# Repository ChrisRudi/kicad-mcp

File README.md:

# Claude für KiCad — Chat-Copilot im PCB-Editor + 186-Tool-MCP-Server

**Claude als dockbares Chat-Panel direkt in KiCad 10** — mit klickbaren
Board-Links, 34 Ein-Klick-Super-Features und einem warmen lokalen MCP-Server —
plus derselbe Server als klassischer [Model Context Protocol](https://modelcontextprotocol.io/)-Endpunkt
für Claude Code, Claude Desktop, Cursor und jeden anderen MCP-Client.

> Deutsche Übersetzung dieser README: [README.de.md](README.de.md).
> (This README is bilingual-pragmatic: product sections in German — the
> plugin UI language — tool/API sections in English.)

---

## What Makes This Different

Most KiCad MCP servers are tool collections. This one is a **product**:

- **💬 Chat dockt in den PCB-Editor** — ein Toolbar-Button öffnet „Claude für
  KiCad" als natives AUI-Panel. Jede Nachricht läuft als headless
  Claude-Code-Turn gegen das **offene Board** (keine API-Keys — dein
  Claude-Code-Login).
- **🔗 Klickbare Antworten (Cross-Probe)** — Referenzen, Netze, Pins, Layer und
  Koordinaten in der Antwort sind Links: Klick markiert + zoomt im Editor.
  Änderungen kommen mit Quittung („✎ geändert: … · 📍 zeigen") und sichtbarem
  **Undo**.
- **✨ 34 Super-Features als Ein-Klick-Buttons** — Dinge, die KiCad
  *prinzipiell* nicht kann, weil sie Bedeutung/Norm-/Datenblatt-Wissen
  brauchen: Entwirren mit Geister-Vorschau, Datenblatt-Abgleich, semantischer
  Design-Wächter, Stromtragfähigkeit (IPC-2221), Schutzklassen (IEC
  61140/60664), echte SPICE-Simulation, BOM-Konsolidierung, DFM-Check … —
  Roadmap + ehrliche Grenzen in [docs/superfeatures.md](docs/superfeatures.md).
- **🔥 Warm-Server** — optional läuft der 186-Tool-Server **einmal pro
  KiCad-Sitzung** als lokaler HTTP-Dienst statt pro Nachricht neu zu starten
  (`KICAD_MCP_TRANSPORT=http`): kein Kaltstart, kein
  „MCP nicht verbunden"-Wackler; Health-Check pro Zug, Auto-Restart,
  Bearer-Token, sauberer Teardown.
- **📐 Generierung, nicht nur Analyse** — Schaltplan + PCB aus
  JSON-Spezifikationen, komplette Projekte aus **ESPHome-YAML**, LTspice-Import,
  Datenblatt-PDF → Applikations-Schaltungsblock.
- **🧭 Ehrlichkeits-Disziplin** — Normwerte (IEC 60664, Fab-Kataloge) leben als
  **datierte, kuratierte Snapshots** im Werkzeug statt im Modellgedächtnis;
  Mutationen laufen nur nach ausdrücklichem **Go**; jede v1-Grenze wird im
  Bericht benannt („Vorprüfung, keine Zertifizierung").
- **🛡️ Gehärtet gegen die fiesen Fälle** — Geister-Editor-Abwehr mit
  Registry + Selbstheilung der Links, Busy-Backoff statt Fehlstart,
  Prozess-Aufräumen bei KiCad-Exit, WSL↔Windows-Pfad-Transparenz.

---

## Die Super-Features (Auszug)

Jeder Button dispatcht einen kanonischen, geführten Auftrag — mit der aktuellen
Editor-**Auswahl** als Wirkbereich (nichts markiert = ganzes Board). Vollständige
Liste + v1-Grenzen: [docs/superfeatures.md](docs/superfeatures.md).

| Button | Was er tut | Fundament |
|---|---|---|
| 🧶 Entwirren | Ratsnest-Entkreuzung: im Kopf lösen, Score vorher/nachher, **Geister-Vorschau auf MCP.Skizze**, ein Batch-Move nach Go | `evaluate_layout`-Scorer |
| 📄 Datenblatt-Abgleich | Beschaltung eines ICs gegen sein PDF (Entkopplung, Pins, fehlende Bauteile) | `review_ic_against_datasheet` |
| 🛡️ Design-Wächter | Semantischer ERC: I²C ohne Pull-ups, Quarz ohne Load-Caps, Entkopplungs-Nähe | `audit_design`-Regel-Registry |
| 🔥 Stromtragfähigkeit | Track-Breiten gegen Design-Strom (IPC-2221, Innenlagen strenger) | `check_ampacity` (#184) |
| 🔌 Schutzklassen | Isolationskonzept nach IEC 61140: geforderte Kriech-/Luftstrecken je Spannungsgrenze aus datiertem Norm-Snapshot vs. Ist-Abstände | `get_safety_spacing` (#186) |
| 📈 Simulation | Echte ngspice-Ausführung des vom Agenten gebauten SPICE-Decks; analytischer Fallback | `run_spice_sim` (#185) |
| 💰 BOM-Konsolidierung / 🏭 Fab-Standardteile | E-Reihen-Standardisierung, No-Load-Fee-Vorzugsteile inkl. Ersparnis | `consolidate_bom`, `suggest_preferred_parts` |
| 🔎 Test-Punkt-Wächter | Kritische Netze ohne Prüfpunkt-Zugang, Abdeckung in % | `audit_test_points` |
| 👁️ Mitdenken-Review | Bewertet deine letzten Hand-Änderungen am offenen Board | `live_summarize_user_changes` |

Dazu: Bus-Radar, Board erklären, Netz-Navigator, Pin-Tausch (Vorschläge),
Ausrichten & Anordnen, Polar-Board, Skizzen-Layer/-Dirigent, Thermik,
Betriebstemperatur, Slew-Rate, Impedanz, DFM-Check, Kosten-Schätzer,
SPICE-Modelle, Bauteil-Sourcing, Foto→Schaltung, Sicherheitsabstände,
Firmware-Pinmap, MLCC-Derating, Silk-Aufräumen, Datenblatt→Schaltung.

---

## ▶ Demo — 10 Referenz-Bausätze

Der **`▶ Demo ▾`**-Knopf im Chat-Panel öffnet ein Menü mit 10 kuratierten
Bausätzen. Jeder fährt den vollen Ablauf **Idee → Schaltplan → Berechnung →
Platine** ab und lässt anschließend die zum Bausatz passende
Super-Feature-Pipeline laufen (z. B. Bus-Radar → semantischer ERC → Impedanz).
So sieht man in einem Klick, was der Copilot produziert — ohne eigenes Board.
Daneben liegt eine **🔧 Schnell-Demo (Testboard)** für den 10-Sekunden-Blick.

**Reife-Label je Bausatz** — zwei unabhängige Achsen, ein Symbol
(`demo_kits.stage`, ein grüner Test, keine Meinung):

- **⭐ Prime-Time** — *beide* Achsen grün: Schaltplan Pin-für-Pin
  datenblatt-geprüft **und** Platine 0 DRC / 0 offene Netze.
- **✅ Verified** — *eine* Achse grün (die andere bewusst oder noch offen).
- **🔬 In Arbeit** — noch keine Achse grün.

**Stand: 8 ⭐ / 2 ✅ / 0 🔬** — alle 10 Platinen bauen DRC-sauber (0 Fehler,
0 offene Netze); Datenblatt-Belege je Bausatz in
[docs/kit_datasheet_reviews.md](docs/kit_datasheet_reviews.md).

| Bausatz | Reife | Was ihn ausmacht |
|---|---|---|
| 🔊 Audioverstärker | ⭐ | Chip-Endstufe mit OpAmp-Eingangsstufe — der Analog-Klassiker (LM386). |
| 🔌 USB-C Sensor-Hub | ⭐ | MCU mit I²C/SPI-Sensoren + USB-C (STM32, LQFP-48) — das Digital-Arbeitstier. |
| ⚡ AC-DC-Netzteil | ⭐ | Offline-Flyback 230 V → 5 V (TNY268) — das Netzspannungs-Projekt. |
| ⚙️ Motor-Treiber | ⭐ | Gate-Driver mit MOSFET-Brücke und MCU (DRV8871) — Leistungselektronik. |
| 📉 Buck-Wandler-Modul | ⭐ | DC-DC-Abwärtswandler mit IC, Spule, Filter-Cs (MP1584). |
| ⊙ LED-Ring | ⭐ | Adressierbare WS2812-LEDs auf rundem Board (Polar-Layout). |
| 🏭 Serienreife & Kosten | ⭐ | Dichtes Breakout mit vielen R/C (74HC595) — Fokus Fertigung & Kosten. |
| 🪄 Datenblatt & Foto → Schaltung | ⭐ | Meta-Demo: wie ein Bausatz überhaupt entsteht. |
| 🌐 Ethernet-Gerät | ✅ | MCU + Ethernet-PHY + RJ45 — Platine ist saubere Referenz (0/0); Schaltplan-Datenblatt-Prüfung noch offen. |
| ✏️ Skizze → Kupfer | ✅ | Kleiner Leistungspfad, den man interaktiv mit Hilfe routet — *bewusst* Skizze. |

Die 10 Spec-JSONs liegen unter `kicad_mcp/resources/data/demo_kits/`; drei
(Buck, Motor, Audio) sind seit 0.27.0 **Build-Artefakte** aus Circuit-Block +
Rezept (eine Quelle, `tests/test_kit_compose.py` wacht). Der ganze Fahrplan,
wie aus den Startplatzierungen 0/0-Platinen wurden:
[docs/roadmap.md](docs/roadmap.md).

---

## Install

### A) Das KiCad-Plugin (empfohlen — Chat + alles oben)

1. Hole `claude_kicad-<version>-pcm.zip`:
   - **Download** aus dem neuesten [GitHub Release](https://github.com/ChrisRudi/kicad-mcp/releases), **oder**
   - **selbst bauen:** `python make_pcm_zip.py` → `dist/claude_kicad-<version>-pcm.zip`
     (pure stdlib, kein KiCad nötig). Alternativ: `install_plugin.bat` /
     `install_plugin.sh` installieren direkt aus dem Repo-Checkout.
2. KiCad: **Plugin- und Content-Manager → Aus Datei installieren…** → Zip wählen.
   (Nicht das GitHub-Auto-Zip nehmen — PCM lehnt den `<repo>-<branch>/`-Wrapper ab.)
3. KiCad neu starten → neuer Toolbar-Button im PCB-Editor. Der erste Klick
   öffnet die Einrichtungs-Checkliste: installiert die Python-Abhängigkeiten in
   einen plugin-eigenen `_deps`-Ordner, aktiviert KiCads IPC-API und hilft beim
   Claude-Code-Login. Danach: Board öffnen, Button klicken, chatten.

Voraussetzungen: **KiCad 10.0**, [Claude Code CLI](https://claude.ai/code)
(Login per Subscription, kein API-Key). Updates liefert der eingebaute
Self-Updater (Versionsanzeige im Panel-Titel; Historie: [plugin/VERSIONS.md](plugin/VERSIONS.md)).

### B) Der MCP-Server für externe Clients

```bash
git clone <this-repo>
cd kicad-mcp

# Linux / WSL / macOS:
./install.sh
# Windows (PowerShell):
.\install.ps1
```

Der Installer prüft KiCad 10, registriert den Server bei Claude Code (falls
`claude` installiert) und druckt Copy-Paste-JSON für Claude Desktop, Cursor,
Windsurf, VS Code, Continue.dev und Zed. Start-Kommandos:
`start_mcp_wsl.sh` (Linux/WSL/macOS) bzw. `start_mcp.bat` (Windows).
Der Server läuft unter **KiCads gebündeltem Python** — keine separate
Python-Installation nötig. Falls KiCad nicht gefunden wird:
`KICAD_PYTHON_PATH` auf die `python.exe` im KiCad-`bin/` setzen.

---

## Warm-Server & Umgebungs-Schalter

Standard-Transport ist `stdio` (Claude startet den Server pro Nachricht).
Mit `KICAD_MCP_TRANSPORT=http` hält das Plugin **einen** persistenten lokalen
Server pro KiCad-Sitzung warm (strikt `127.0.0.1`, zufälliges Bearer-Token,
Pidfile-Verwaltung, Health-Check je Zug, `atexit`-Teardown). Rollback ist
jederzeit ein Env-Wort.

| Variable | Wirkung |
|---|---|
| `KICAD_MCP_TRANSPORT` | `stdio` (Default) oder `http` (Warm-Server) |
| `KICAD_MCP_HTTP_HOST` / `_PORT` / `_TOKEN` | HTTP-Bind + Token (setzt normal das Plugin) |
| `KICAD_MCP_NGSPICE` | Pfad zum ngspice-Binary für `run_spice_sim` (sonst PATH/KiCad-bin) |
| `KICAD_MCP_NO_AUTO_OPEN` | `1` = Server darf nie selbst einen Editor starten (setzt das Plugin automatisch — verhindert Geister-Instanzen) |
| `KICAD_MCP_IPC_TIMEOUT_MS` | kipy-Timeout (Default 15000) |
| `KICAD_MCP_MAX_TURNS` | Agentic-Turn-Limit pro Nachricht (Default 80, 0 = aus) |
| `KICAD_MCP_CONNECT_RETRIES` | Auto-Retry bei MCP-Kaltstart-Fehlschlag (Default 1) |
| `KICAD_PYTHON_PATH` / `KICAD_MCP_ROOT` / `KICAD_BIN` | Pfad-Overrides (KiCad-Python, Server-Code, kicad-cli) |
| `KICAD_MCP_STATE_DIR` | Ablage des Warm-Server-Pidfiles |
| `KICAD_CLAUDE_ALLOW_WSL` | Opt-in: Windows-KiCad + Claude in WSL (Bridge) |

Diagnose: Der **Diagnose-Knopf** im Einrichtungs-Panel sammelt Pfade, Versionen,
Transport-Status (läuft der Warm-Server? PID, Port, Uptime, MCP-Ping) und die
echte Server-Probe in einen kopierbaren Report.

---

## Tool-Familien (186 Tools)

Single Source of Truth ist [`kicad_mcp/tool_registry.py`](kicad_mcp/tool_registry.py)
(der Drift-Wächter `tests/test_tool_audit.py` pinnt die Zahl); jede
Tool-Docstring erklärt „wann dieses, wann das Nachbar-Tool". Die Familien:

| Familie | Highlights |
|---|---|
| **Analyse (SCH/PCB)** | `list_pcb_footprints`, `analyze_pcb_nets`, `find_tracks_by_net`, `list_schematic_components`, Pin-/Pattern-Analyse, `get_board_stats` |
| **Validierung** | `run_erc` / `run_drc_check` (kicad-cli, headless), DRC-Historie, `validate_design` |
| **Semantik-Audits** | `audit_design` (Regel-Registry), `audit_power_tree`, `audit_test_points`, `list_bus_members`, `consolidate_bom`, `suggest_preferred_parts` |
| **Elektrik/Norm** | `check_ampacity` (IPC-2221), `get_safety_spacing` (IEC-60664-Snapshot), `run_spice_sim` (ngspice-Batch) |
| **Export** | Gerber, Drill, STEP, PDF/SVG/PNG, Pick&Place, 3D-Render, BOM/Netzliste |
| **Generierung** | `generate_project` / `generate_schematic` / `generate_pcb` aus JSON, `generate_from_netlist`, `esphome_to_kicad`, `convert_ltspice_to_kicad` |
| **PCB-Text-Patcher** (headless, F8-äquivalent) | Netz-Tagging aus Netzliste, Footprint-Resolve, Rotation, `pcb_batch` (N Edits, eine Write-Runde), `add_vias_to_pcb`, `place_at_pivot` |
| **PCB-Geometrie/Routing** | flip-/rotations-korrekte Welt-Koordinaten (`compute_pad_world_positions`), Tracks/Bögen/Zonen, `polar_grid` (Radial-Layouts) |
| **Schaltplan-Patcher** (inkrementell, headless) | Symbole/Wires/Labels einfügen, `connect_pins`, Gruppen-Transformationen, Annotation, `add_power_symbols` |
| **IPC-Live-Bridge** (laufende KiCad-GUI) | Tracks/Vias/Zonen/Pose live, Save/Revert, Selektion (`ipc_get_selection`), Marker/Skizzen-Layer (`ipc_draw_markers`, `ipc_markup_to_tracks`), Live-Diff (`live_summarize_user_changes`) |
| **Warm-Board-Daemons** | `pcb_eval` (Ad-hoc-Geometrie gegen warmes Board), `check_connectivity` (headless Ratsnest), `via_promote` (Blind/Buried→Through) |
| **Review/Datenblatt** | `review_ic_against_datasheet`, `review_system_interconnect`, `list_missing_datasheets`, `extract_circuit_from_pdf` → `apply_circuit_block` |
| **Rendering** | `pcb_render` (Region-PNGs statt Kopf-Geometrie) |
| **Footprint-Suche** | Index über die gebündelte KiCad-Bibliothek, Spec-basierte Suche, Alternativen-Vorschlag |
| **Projekt/Diagnose** | Projekt-Discovery, `kicad_mcp_doctor`, Benchmarks |

---

## Architektur in einem Absatz

Der Server läuft unter KiCads gebündeltem Python (kipy + pcbnew erreichbar) und
spricht wahlweise stdio oder streamable-HTTP. Drei Editier-Wege, je nach
Situation: **Text-Patcher** (chirurgische `.kicad_pcb`/`.kicad_sch`-Edits,
headless), **IPC-Live-Tools** (mutieren das In-Memory-Modell der offenen GUI —
Pflicht, wenn das Board offen ist; ein Disk-Write-Guard blockt Kollisionen)
und **Generatoren** (neue Dateien aus Specs). Ein zentraler kipy-Session-Layer
recycelt die Verbindung mit Health-Check und Busy-Backoff; Warm-Board-Daemons
amortisieren Load+Fill über wiederholte Abfragen; ein stat-revalidierter
File-Cache killt redundante Reads. Verhaltensregeln gegen
Toolcall-Explosionen (nicht nach jeder Mini-Änderung rendern, Batch vor
Einzeln, Result lesen statt Rücklesen) stehen in [CLAUDE.md](CLAUDE.md) und in
jeder Mutations-Docstring.

Bekannte KiCad-10-Grenze: Eeschema hat kein IPC-Save/RunAction (KiCad #2077) —
Schaltplan-Edits laufen dateibasiert bei geschlossenem Eeschema, Live-ERC über
`kicad-cli`. Der 3D-Viewer hat keine API.

---

## Credits & Origins

This project builds on the work of others and adds significant new functionality:

### [lamaalrajih/kicad-mcp](https://github.com/lamaalrajih/kicad-mcp) — Foundation

The core server architecture, including FastMCP integration, async tool
registration, project discovery, DRC with history tracking, BOM analysis,
netlist extraction, circuit pattern recognition, and the security layer (path
validation, secure subprocess runner). Originally MIT licensed upstream; this
fork as a whole is GPL-3.0-or-later (see [License](#license)).

### [Seeed-Studio/kicad-mcp](https://github.com/nicholasgasior/kicad-mcp) — Inspiration

Conceptual model for ERC integration, schematic/PCB analysis tools, pin
function inference, and hierarchical sheet handling. The implementations here
are rewritten from scratch on our own S-expression parser.

### Built for This Project

Everything else: the KiCad chat plugin (docked panel, cross-probe links,
change receipts, super-feature bar, setup/diagnose, self-updater, warm-server
lifecycle), the S-expression engine, schematic/PCB generation from JSON,
ESPHome/LTspice converters, the PCB text-patcher + geometry/routing layers,
the schematic-patch layer, the IPC live bridge incl. sketch-layer tooling and
live diff, warm-board daemons, the semantic audit registry, the norm/physics
tools (`check_ampacity`, `run_spice_sim`, `get_safety_spacing` with dated
standards snapshots), footprint search, `pcb_render`, and the cross-environment
path layer (WSL ↔ Windows).

---

## Generation Input Format

The generation tools accept JSON strings. Example:

```json
{
  "parts": [
    {
      "ref": "U1",
      "name": "ESP32-C6",
      "footprint": "RF_Module:ESP32-C6-MINI-1",
      "value": "ESP32-C6",
      "pins": [
        {"num": 1, "name": "VCC", "type": "power_in"},
        {"num": 2, "name": "GND", "type": "power_in"},
        {"num": 3, "name": "IO17", "type": "bidirectional"}
      ]
    },
    {
      "ref": "R1",
      "name": "R",
      "footprint": "Resistor_SMD:R_0805_2012Metric",
      "value": "10k",
      "pins": [
        {"num": 1, "name": "1", "type": "passive"},
        {"num": 2, "name": "2", "type": "passive"}
      ]
    }
  ],
  "nets": [
    {"name": "VCC", "type": "power", "connections": ["U1:VCC", "R1:1"]},
    {"name": "GND", "type": "power", "connections": ["U1:GND", "R1:2"]},
    {"name": "SDA", "type": "signal", "connections": ["U1:IO17"]}
  ],
  "board": {"shape": "rectangle", "width": 50, "depth": 30, "layers": 2, "thickness": 1.6}
}
```

**Pin types:** `input`, `output`, `bidirectional`, `tri_state`, `passive`,
`power_in`, `power_out`, `open_collector`, `open_emitter`, `free`,
`unspecified`, `no_connect` · **Board shapes:** `rectangle`, `circle`,
`euro_divider` (`euro_type`: `3U`, `6U`, `half_euro`)

---

## ESPHome YAML to KiCad

Paste an ESPHome YAML config and get a complete KiCad project — ESP module
with correct pinout, sensors on their buses with pull-ups, decoupling caps per
IC, power nets, `.kicad_sch` + `.kicad_pcb` + `.kicad_pro`:

```yaml
esphome: {name: weather-station}
esp32: {board: esp32dev}
i2c: {sda: 21, scl: 22}
sensor:
  - {platform: bme280, address: 0x76}
  - {platform: bh1750, address: 0x23}
light:
  - {platform: neopixelbus, pin: GPIO16, num_leds: 30}
```

**Supported platforms:** BME280, BME680, DHT22, DS18B20, SHT31, BH1750,
VL53L0X, MPU6050, ADS1115, SSD1306, WS2812B — extendable via the component
database. Add `simulation=True` for SPICE-ready schematics.

---

## Process Supervisor (optional, stdio clients)

`_tasks/mcp_supervisor/` ships a thin JSON-RPC-transparent wrapper for
external stdio clients: auto-respawn on child crash + an injected
`restart_mcp_child` tool for wedged sessions. Point your client at
`start_mcp_supervisor.sh` instead of `start_mcp_wsl.sh`; details in
`_tasks/mcp_supervisor/README.md`. (The in-KiCad plugin doesn't need it — the
warm-server manager has its own health-check/restart cycle.)

---

## Development

```bash
pip install -e ".[dev]"
pytest tests/          # ~2700 tests; KiCad-/kipy-gebundene skippen headless
pylint --rcfile=pyproject.toml --disable=C,R kicad_mcp tests   # CI-Gate: 0/0
sh scripts/setup-hooks.sh   # einmalig: pre-commit spiegelt kicad_mcp/ → plugin/mcp/
```

Konventionen für neue Tools (Pfad-Normalisierung, Registry, Batch-Companions,
Tests, Tool-Count-Wächter) stehen in [CLAUDE.md](CLAUDE.md). Logs:
`~/.kicad-mcp/logs/kicad-mcp.log`; IPC-Log neben dem Board
(`kicad_mcp_ipc.log`).

---

## License

**GPL-3.0-or-later** — see [LICENSE](LICENSE).

This project loads KiCad's `pcbnew` Python module in-process (for PCB geometry,
connectivity and via analysis). `pcbnew` is part of KiCad and licensed under
GPL-3.0; combining with it makes the project as a whole GPL-3.0-or-later. See
[NOTICE](NOTICE) for the rationale and third-party components.

Portions derive from the upstream [kicad-mcp](https://github.com/lamaalrajih/kicad-mcp)
by Lama Al Rajih, originally under the MIT License (GPL-compatible) — the
original notice is preserved in [LICENSE.MIT](LICENSE.MIT).

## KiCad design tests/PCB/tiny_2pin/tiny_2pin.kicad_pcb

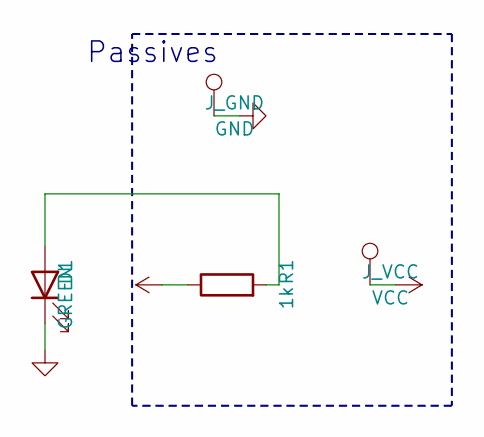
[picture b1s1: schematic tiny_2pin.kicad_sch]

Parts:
D1: GREEN; LED_0805_2012Metric
J_GND: GND; TestPoint_Pad_D2.0mm
J_VCC: VCC; TestPoint_Pad_D2.0mm
R1: 1k; R_0805_2012Metric

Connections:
GND: D1.1 (K), J_GND.1
NET_R_LED: D1.2 (A), R1.2
VCC: J_VCC.1, R1.1

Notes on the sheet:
Passives

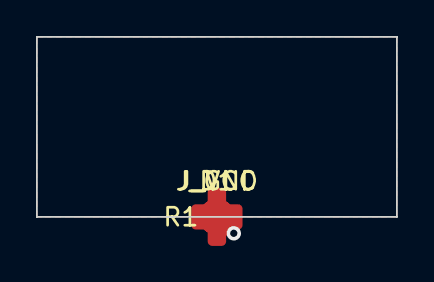
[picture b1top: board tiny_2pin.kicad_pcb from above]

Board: 2 copper layers, 20.0 x 10.0 mm, 4 parts (0 on the bottom side), 3 nets.

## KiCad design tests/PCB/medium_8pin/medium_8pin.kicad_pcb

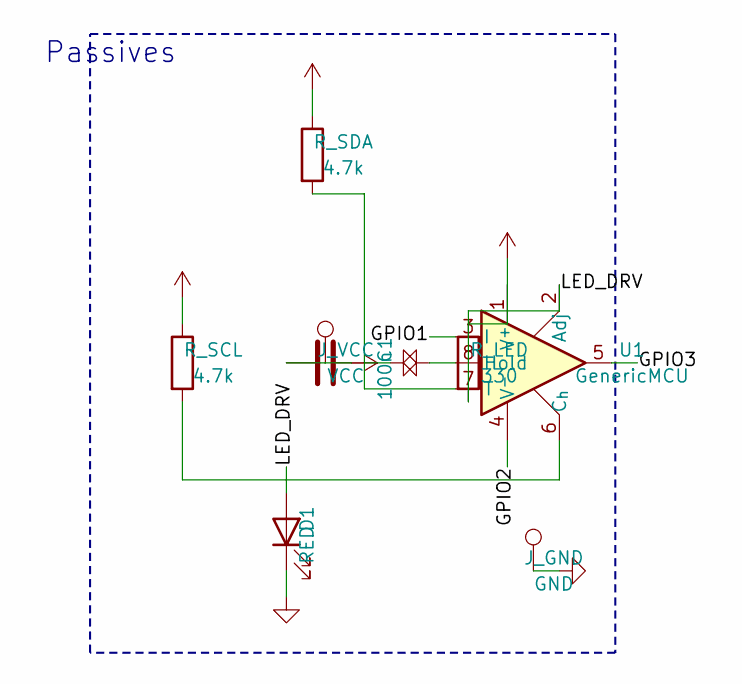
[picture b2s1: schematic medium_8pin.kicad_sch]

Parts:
C1: 100n; C_0402_1005Metric
D1: RED; LED_0805_2012Metric
J_GND: GND; TestPoint_Pad_D2.0mm
J_VCC: VCC; TestPoint_Pad_D2.0mm
R_LED: 330; R_0402_1005Metric
R_SCL: 4.7k; R_0402_1005Metric
R_SDA: 4.7k; R_0402_1005Metric
U1: GenericMCU; SOIC-8_3.9x4.9mm_P1.27mm

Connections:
GND: C1.2, D1.1 (K), J_GND.1, U1.8 (Hold)
GPIO1: U1.3 (I)
GPIO2: U1.4 (V^{-})
GPIO3: U1.5
LED_DRV: D1.2 (A), R_LED.2, U1.2 (Adj)
SCL: R_SCL.2, U1.6 (C_{h})
SDA: R_SDA.2, U1.7 (T)
VCC: C1.1, J_VCC.1, R_LED.1, R_SCL.1, R_SDA.1, U1.1 (V^{+})

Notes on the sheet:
Passives

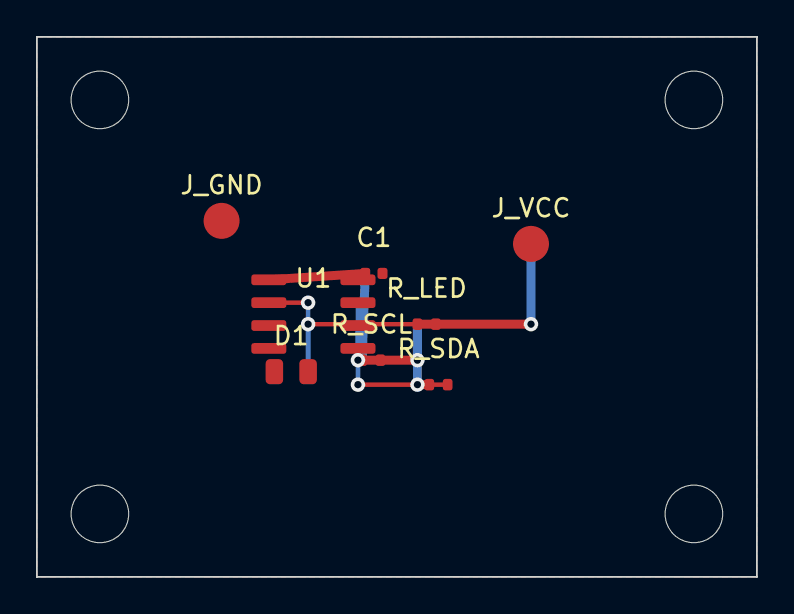
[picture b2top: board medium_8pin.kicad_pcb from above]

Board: 2 copper layers, 40.0 x 30.0 mm, 12 parts (0 on the bottom side), 5 nets.

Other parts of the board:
MH1, MH2, MH3, MH4: MountingHole; MountingHole_3.2mm_M3

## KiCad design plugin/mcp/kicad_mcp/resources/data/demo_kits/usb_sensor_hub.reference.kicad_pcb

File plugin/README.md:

# Claude für KiCad — Action-Plugin (Stufe 1)

Ein KiCad-PCB-Editor-Plugin mit Toolbar-Button **„Claude"**, das ein Chat-Panel
öffnet. Du tippst eine Frage/Anweisung zum offenen Board, das Plugin fährt einen
**Claude-Code**-Turn (dein Abo, *keine* API-Kosten) über den gebündelten
**kicad-mcp**-Server, und zeigt die Antwort. Claude arbeitet dabei live am Board.

```
[Chat-Panel in KiCad]  →  claude -p (Abo)  →  kicad-mcp  →  IPC  →  dieselbe pcbnew
        ▲                                                              │
        └────────────────────  Antwort + Board-Aktionen  ◀────────────┘
```

## Läuft auf Windows UND Linux — kein WSL nötig
Das Plugin läuft in KiCads eigenem Python, also in **KiCads Betriebssystem**.
Claude Code und der kicad-mcp-Server laufen im **selben** System — dadurch sind
alle Pfade in einem Stil und es gibt keine Cross-OS-Brüche:

| KiCad | Claude Code | Modus |
|---|---|---|
| Windows | Windows-`claude` | nativ (alle `C:\…`-Pfade) |
| Linux/mac | lokaler `claude` | nativ (alle `/…`-Pfade) |

> **WSL ist nicht erforderlich.** Ein Entwickler, der Claude bereits in WSL hat,
> kann die WSL-Brücke per `KICAD_CLAUDE_ALLOW_WSL=1` einschalten — standardmäßig
> ist sie aus, und niemand wird je aufgefordert, WSL zu installieren.

## Einmal-Setup (das, was kein Plugin abnehmen kann)
1. **Claude Code installieren** (im selben System wie KiCad — auf Windows der
   Windows-Installer/`npm`, *kein* WSL) und **einloggen**: `claude` muss
   aufrufbar sein, einmal `claude login` (dein Anthropic-Abo).
2. **Projekt-Vertrauen**: einmal `claude` *interaktiv* im Projektordner starten,
   damit der Trust-Dialog durch ist (Headless-`-p` fragt nicht nach).
3. **kicad-mcp** muss erreichbar sein. Falls nicht am Default-Pfad, setze:
   - `KICAD_MCP_ROOT` = Ordner des `kicad-mcp`-Repos (mit `kicad_mcp/`)
   - `KICAD_PYTHON_PATH` = KiCad-Python mit `kipy`
     (z. B. `C:\Program Files\KiCad\10.0\bin\python.exe`)

Schritt 1+2 macht der **Einrichtungs-Check** beim ersten Klick mit Ein-Klick-
Knöpfen (Installieren / Anmelden) so weit wie möglich selbst.

## Plugin installieren

**KiCad-PCM (Aus Datei installieren):** Eine **PCM-konforme ZIP** (NICHT die GitHub-Repo-ZIP
— die hat das falsche Layout) bauen und in KiCad einspielen:

```bash
python make_pcm_zip.py        # erzeugt dist/claude_kicad-<version>-pcm.zip
```
Dann in KiCad: **Plugin and Content Manager → Aus Datei installieren…** → die ZIP wählen.
(Bei Releases hängt die GitHub-Action `pcm-zip` diese ZIP automatisch als Asset an — dann
einfach von der Release-Seite laden.) Danach Claude-Button anklicken; das Einrichtungs-Panel
macht den Rest. Hinweis: KiCads PCM erwartet als Add-on-ZIP genau dieses Layout
(`metadata.json` an der Wurzel + `plugins/` + `resources/`), das die Repo-ZIP nicht hat.

**Ein-Klick-Skript:** Skript aus dem Repo-Root ausführen — es holt das Plugin
(git oder ZIP-Fallback) und kopiert es an die richtige Stelle:

- **Windows:** `install_plugin.bat` herunterladen, Doppelklick (optional KiCad-Version als
  Argument, Default `10.0`).
- **Linux/macOS:**
  ```bash
  curl -fsSL https://raw.githubusercontent.com/ChrisRudi/kicad-mcp/main/install_plugin.sh | bash
  ```

**Manuell:** Kopiere den `plugin/`-Ordner in KiCads Plugin-Verzeichnis und benenne ihn
`claude_kicad`:
- Windows: `%APPDATA%\kicad\10.0\scripting\plugins\claude_kicad\`
- Linux: `~/.local/share/kicad/10.0/scripting/plugins/claude_kicad/`
- macOS: `~/Library/Application Support/kicad/10.0/scripting/plugins/claude_kicad/`

Dann in pcbnew: **Werkzeuge → Externe Plugins → Aktualisieren** (oder KiCad neu
starten). Der **Claude**-Button erscheint in der Toolbar.

> **Wichtig — nicht aus der Konsole importieren.** Lade das Plugin ausschließlich
> über den Plugin-Ordner + **Aktualisieren**. Ein `import` im Scripting-Terminal
> (oder unter dem nackten KiCad-`python.exe`) löst den C++-Assert
> `PgmOrNull() … register_action()` aus, weil dort kein laufendes GUI existiert.
> Das Plugin registriert sich deshalb nur, wenn eine echte `wx.App` läuft.

## Erster Klick: Einrichtungs-Check
Beim ersten Mal (oder sobald etwas fehlt) öffnet der Button ein
**Einrichtungs-Panel** — eine grün/rote Checkliste mit je einem Ein-Klick-Fix:

| Prüfung | grün = | Fix-Knopf |
|---|---|---|
| Claude Code gefunden | `claude` aufrufbar | **Installieren** (offizieller Installer) |
| KiCad-Python (kipy) | `python.exe` mit kipy gefunden | **Hilfe** (Env-Vars) |
| kicad-mcp bereit | `KICAD_MCP_ROOT` enthält `kicad_mcp/` | **Hilfe** |
| Angemeldet & Ordner vertraut | `claude login` + Projekt getrustet | **Anmelden** (Terminal) |
| MCP-Abhängigkeiten | fastmcp/mcp/pandas/… in KiCad-Python | **Installieren** (pip --user) |
| KiCad-API aktiv | IPC-Server an (für Live-Arbeit am Board) | **Aktivieren** |
| Board offen | ein `.kicad_pcb` ist offen | — |

**Claude Code installiert der Knopf wirklich** (nicht nur Doku): er zeigt erst
den exakten **offiziellen** Befehl (Windows `irm https://claude.ai/install.ps1 |
iex`, Linux/mac `curl -fsSL https://claude.ai/install.sh | bash`), und öffnet
nach Bestätigung ein **sichtbares** Terminal, das ihn ausführt — kein stilles
`curl|bash`. Der Installer legt `claude` in `~/.local/bin` ab; das Plugin findet
ihn dort sofort (kein KiCad-Neustart nötig). Der eine interaktive Rest bleibt:
einmal `claude login` (OAuth) — dafür ist der **Anmelden**-Knopf da.

**KiCad-API (IPC) wird automatisch aktiviert.** Beim ersten Klick setzt das
Plugin `api.enable_server` in `kicad_common.json` (der Schalter hinter
*Einstellungen → Plugins → KiCad-API*) und sagt dir, dass du KiCad **einmal neu
starten** musst — der IPC-Server startet nur beim Programmstart. Es schreibt nur
diesen einen Schlüssel, alle anderen Einstellungen bleiben unangetastet, und es
ist idempotent (re-asserted bei jedem Laden, falls KiCad ihn je zurücksetzt).

**Chat starten** wird aktiv, sobald kein harter Fehler (rot) mehr offen ist
(Warnungen sind nur Hinweise). Ist beim Klick schon alles grün, springt der
Button direkt in den Chat — das Panel erscheint dann gar nicht.

## Benutzen
1. Board in pcbnew öffnen.
2. **Claude**-Button klicken → Einrichtungs-Check (einmalig) → Chat-Panel.
3. Tippen, z. B.:
   - „wie viele GND-Vias hat das Board?"
   - „markier die 3 kleinsten Vias"
   - „setz ein GND-Via bei 140,110"

Das Panel ist **nicht-modal** — du siehst das Board live aktualisieren, während
Claude arbeitet. Der Gesprächsfaden bleibt über mehrere Nachrichten erhalten
(`--resume` mit der Session-ID aus der ersten Antwort).

## Was wo läuft (Stufe 1)
| Datei | Aufgabe |
|---|---|
| `__init__.py` | registriert den Button — **nur bei laufender `wx.App`** (sonst Assert) |
| `claude_action.py` | Klick → Preflight → Einrichtungs-Panel **oder** direkt Chat |
| `setup_dialog.py` | wx-Einrichtungs-Panel (grün/rote Checkliste + Fix-Knöpfe) |
| `chat_dialog.py` | wx-Chat-Panel (Ein-/Ausgabe, Worker-Thread) |
| `runtime_env.py` | löst pro Maschine einen pfad-konsistenten RunPlan (nativ Win/Linux, opt-in WSL-Brücke) (testbar) |
| `ipc_setup.py` | aktiviert KiCads IPC-API (`api.enable_server` in `kicad_common.json`) (testbar) |
| `installer.py` | offizielle Claude-Code-Install-Befehle + sichtbares Install-Terminal (testbar) |
| `deps.py` | prüft/installiert die MCP-Server-Laufzeit-Deps (fastmcp/pandas/…) in KiCad-Python (testbar) |
| `mcp/kicad_mcp/` | **gebündelte** Kopie des kicad-mcp-Servers (self-contained; ohne `.cache`/`__pycache__`) |
| `preflight.py` | reine Detektoren (Claude/Python/MCP/Login/Board) (testbar) |
| `claude_bridge.py` | `claude -p … --mcp-config … --resume …`, JSON-Antwort (testbar) |
| `mcp_config.py` | erzeugt die `--mcp-config`-JSON für kicad-mcp (testbar) |

`runtime_env.py`, `ipc_setup.py`, `installer.py`, `deps.py`, `updater.py`,
`claude_bridge.py`, `mcp_config.py` und `preflight.py` sind reine Logik (keine
KiCad-Imports), headless getestet in `tests/test_plugin_*.py` (98 Tests).

## Self-contained (gebündeltes MCP)
Das Plugin liefert eine Kopie des kicad-mcp-Servers in `mcp/kicad_mcp/` mit. Die
MCP-Wurzel wird so aufgelöst: `KICAD_MCP_ROOT` (falls gesetzt & gültig) →
**gebündeltes `mcp/`** → Dev-Checkout-Fallback. Damit läuft das Plugin auf
fremden Rechnern ohne Repo-Pfad. Die **Laufzeit-Deps** (fastmcp/mcp/pandas/
pyyaml/defusedxml/jsonschema) sind nicht in KiCads Python — der Onboarding-Check
*MCP-Abhängigkeiten* installiert sie per `pip --user` (kein Admin).

## Icon
Der Toolbar-Button trägt das **offizielle Model-Context-Protocol-Logo**
(`icon.png` hell / `icon_dark.png` dunkel, aus der MCP-SVG gerendert). Bewusst
das MCP- statt eines Claude-Logos: MCP ist der **offene, anbieterneutrale**
Standard — das Icon signalisiert „spricht MCP", nicht einen bestimmten Anbieter.
Lizenz des Logos: MIT bzw. unterhalb der Schöpfungshöhe (faktisch gemeinfrei,
Quelle Wikimedia Commons / `modelcontextprotocol`); in manchen Ländern als Marke
schützbar — Verwendung nur als Kompatibilitäts-Hinweis, ohne Anthropic-Billigung
zu suggerieren. Zum Tauschen einfach `icon.png` / `icon_dark.png` ersetzen
(quadratisch, transparent; ~48 px).

## Sicherheit (ehrlich)
Stufe 1 nutzt `--dangerously-skip-permissions`, damit Claude im Headless-Modus
ohne TTY-Rückfrage die kicad-mcp-Tools ausführen darf. Das heißt: **alle**
kicad-mcp-Tools laufen ungefragt. Da der MCP-Server lokal + von dir kontrolliert
ist, ist das vertretbar — aber jede Board-Änderung ist in pcbnew **undo-bar**
(Bearbeiten → Rückgängig, „kicad-mcp …"). Spätere Stufe: `--permission-mode`
/ `--allowedTools` für feinere Kontrolle.

## Updates (zwei Wege)
Das Plugin trägt eine **Version** (`version.py`, im Panel-/Chat-Titel sichtbar).

1. **Direkt aus GitHub (vorläufig, zum Testen):** Im Einrichtungs-Panel
   *Update prüfen* — liest `plugin/version.py` aus `ChrisRudi/kicad-mcp`, und
   lädt bei neuerer Version das Branch-Zip, überschreibt die `plugin/`-Dateien
   in place. Danach **KiCad neu starten**. (Erreichbar auch aus dem Chat über
   *Einrichtung / Update*.) Nur dieses eine Repo, über HTTPS — Update aus dem
   Netz ist Code-Ausführung, also nie auf eine fremde Quelle zeigen.
2. **Offizielles KiCad-PCM (Ziel):** sobald alles läuft, Einreichung ans
   offizielle Metadaten-Repo (`gitlab.com/kicad/addons/metadata`) → erscheint im
   *Plugin and Content Manager* bei **allen** KiCad-Nutzern (Update/Deinstall in
   der GUI). Voraussetzung: das Paket self-contained machen (kicad-mcp bündeln).

Branch überschreibbar per `KICAD_MCP_PLUGIN_BRANCH` (Default `main`).

## Roadmap
- **Stufe 1 ✓:** Button → Einrichtungs-Check → Chat über Claude Code + kicad-mcp.
- **Stufe 2:** Backend-Auswahl (Claude Code / Codex / …) im Panel.
- **Stufe 3:** kicad-mcp in den Plugin-Ordner bündeln (Default-`KICAD_MCP_ROOT`
  wird dann der mitgelieferte Ordner statt eines Repo-Pfads) → Paket
  self-contained → MR ans offizielle PCM-Metadaten-Repo (alle KiCad-Nutzer).

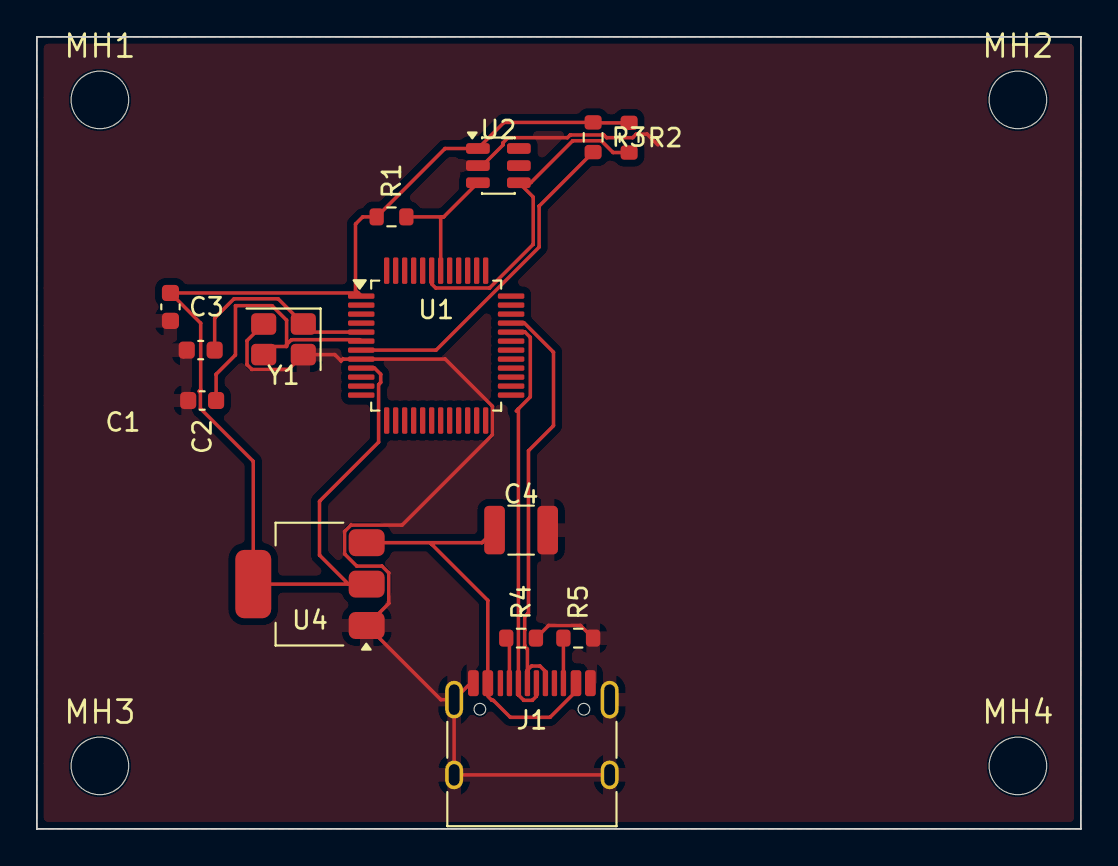
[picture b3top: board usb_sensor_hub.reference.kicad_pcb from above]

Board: 2 copper layers, 58.0 x 44.0 mm, 18 parts (0 on the bottom side), 12 nets.

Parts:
C1, C2: 20p; C_0603_1608Metric
C3: 100n; C_0603_1608Metric
C4: 10u; C_1210_3225Metric
J1: USB-C; USB_C_Receptacle_HRO_TYPE-C-31-M-12
MH1, MH2, MH3, MH4: MountingHole; MountingHole_3.2mm_M3
R1, R2: 4k7; R_0603_1608Metric
R3: 10k; R_0603_1608Metric
R4, R5: 5k1; R_0603_1608Metric
U1: STM32F103C8; LQFP-48_7x7mm_P0.5mm
U2: BME280; SOT-23-6
U4: AMS1117-3.3; SOT-223-3_TabPin2
Y1: 8MHz; Crystal_SMD_3225-4Pin_3.2x2.5mm

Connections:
CC1: J1.A5, R4.1
CC2: J1.B5, R5.1
GND: C1.2, C2.2, C3.2, C4.2, J1.A1, J1.A12, J1.B1, J1.B12, J1.SH, R4.2, R5.2, U1.8, U2.2, U4.1, Y1.2, Y1.4
NRST: R3.2, U1.7
OSC_IN: C1.1, U1.5, Y1.1
OSC_OUT: C2.1, U1.6, Y1.3
P3V3: C3.1, R1.1, R2.1, R3.1, U1.1, U1.9, U2.1, U4.2
SCL: R1.2, U1.42, U2.3
SDA: R2.2, U1.43, U2.4
USB_DM: J1.A7, J1.B7, U1.32
USB_DP: J1.A6, J1.B6, U1.33
VBUS: C4.1, J1.A4, J1.A9, J1.B4, J1.B9, U4.3

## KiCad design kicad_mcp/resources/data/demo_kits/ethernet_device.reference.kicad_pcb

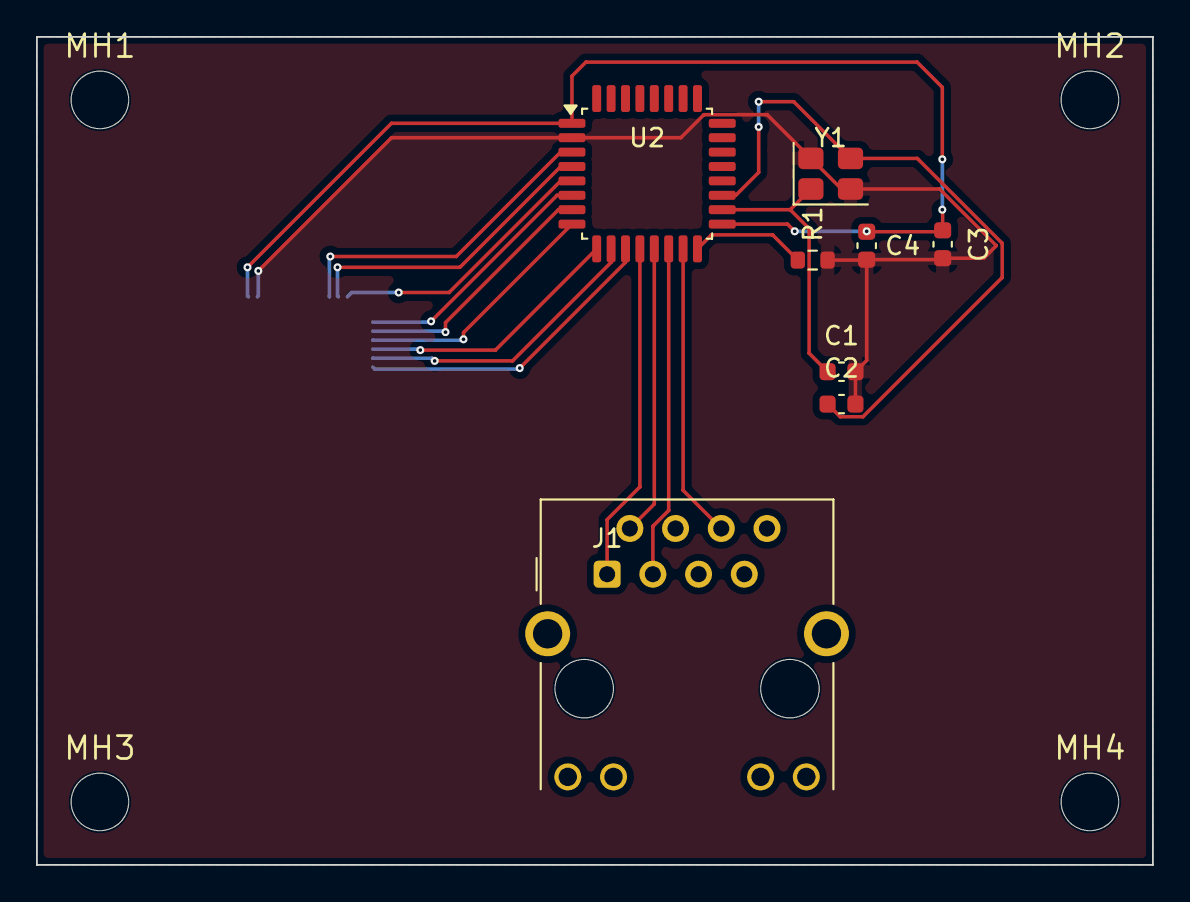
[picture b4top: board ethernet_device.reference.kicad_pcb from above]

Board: 2 copper layers, 62.0 x 46.0 mm, 13 parts (1 on the bottom side), 18 nets.

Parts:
C1, C2: 18p; C_0603_1608Metric
C3, C4: 100n; C_0603_1608Metric
J1: RJ45_Magjack; RJ45_HanRun_HR911105A
MH1, MH2, MH3, MH4: MountingHole; MountingHole_3.2mm_M3
R1: 12k1; R_0603_1608Metric
U1: STM32F407; LQFP-48_7x7mm_P0.5mm
U2: LAN8720; LQFP-32_7x7mm_P0.8mm
Y1: 25MHz; Crystal_SMD_3225-4Pin_3.2x2.5mm

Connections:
CRS_DV: U1.13, U2.6
ETH_RXN: J1.6, U2.15
ETH_RXP: J1.3, U2.14
ETH_TXN: J1.2, U2.13
ETH_TXP: J1.1, U2.12
GND: C1.2, C2.2, C3.2, C4.2, R1.2, U1.2, U2.2, Y1.2, Y1.4
MDC: U1.11, U2.4
MDIO: U1.12, U2.5
P3V3: C3.1, C4.1, U1.1, U2.1, U2.17
RBIAS: R1.1, U2.16
REF_CLK: U1.10, U2.3
RXD0: U1.14, U2.7
RXD1: U1.15, U2.8
TXD0: U1.17, U2.10
TXD1: U1.18, U2.11
TXEN: U1.16, U2.9
XI: C1.1, U2.18, Y1.1
XO: C2.1, U2.19, Y1.3

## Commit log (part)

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2026-06-11 Plugin-Chat: schwarzes Konsolenfenster unter Windows unterdrücken
    Der claude-p-Kindprozess wird aus der KiCad-GUI heraus gestartet; Windows
    öffnete dafür pro Chat-Runde ein sichtbares cmd-Fenster, das aufblitzt und
    sich wieder schließt. Neue Helper-Funktion hidden_console_kwargs() gibt
    unter Windows CREATE_NO_WINDOW + stdin=DEVNULL mit (gilt auch für den
    'wsl claude'-Fallback); auf POSIX no-op. Die Antwort lief schon immer per
    Pipe ins Chat-Panel — am Verhalten ändert sich sonst nichts.
2026-06-11 Plugin v0.2.7: Chat-Panel dockt als natives AUI-Pane in den PCB-Editor
    Das Chat-Fenster snapt jetzt in KiCad: neues plugin/dock.py hängt das
    Panel über wx.aui.AuiManager.GetManager(PcbFrame) als AUI-Pane in den
    PCB-Editor ein — andocken an die Fensterränder, abreißen, verschieben,
    Größe ziehen, wieder andocken wie bei Darstellung/Suche; die Position
    landet in KiCads gespeicherter Perspective (stabile Pane-Id).
    Dafür ist das UI von ClaudeChatDialog in ein wiederverwendbares
2026-06-11 Plugin v0.2.9: Deps in plugin-eigenen Ordner + Presence-Beacon mutiert das Board nicht mehr
    Zwei User-Reports behoben:
    1) 'KiCad hat ungespeicherte Aenderungen' nach jedem MCP-Kontakt:
    Der Presence-Beacon hat beim ersten IPC-Kontakt die Skizzen-Ebene
    im Board-Setup aktiviert und die Legende aufs Board gestempelt --
    beides macht das Board 'modified', bei jedem Neustart erneut (jeder
    Chat-Turn ist ein frischer Server-Prozess). Der Beacon ist jetzt
2026-06-12 Plugin v0.2.11: Datei-Schreibverbot fuer Claude + Server-Probe als echter MCP-Handshake
    Zwei Field-Reports:
    1) 'Es macht alle Dateien an die es sieht' + Dauermeldung 'ungespeicherte
    Aenderungen' (auch Projektfile): Ohne verbundenen MCP hat Claude die
    Board-Fragen beantwortet, indem es .kicad_pcb/.kicad_sch/.kicad_pro
    mit den eingebauten Tools DIREKT editierte (Chat laeuft headless mit
    --dangerously-skip-permissions). KiCad sieht externe Edits an offenen
2026-06-12 Plugin v0.2.13: Install-Terminal zeigt den _deps-Zielordner
    Der Terminal-Output war fast vollstaendig diagnostizierbar (Python-Pfad,
    pip-Quelle, Verifikation) -- nur WOHIN installiert wird fehlte. Jetzt
    steht 'Ziel-Ordner (_deps): <pfad>' mit drin, womit alle beteiligten
    Pfade direkt ablesbar sind.
    https://claude.ai/code/session_01Rxpc5X1arT1U2qtb2bFJ8H
2026-06-12 Plugin v0.2.15: Root-Cause-Fix -- KiCads Python ignoriert PYTHONPATH, Server-Start per -c-Bootstrap
    Experimentell auf der betroffenen Maschine bestaetigt:
    set PYTHONPATH=<plugin>\mcp;<plugin>\_deps
    python -m kicad_mcp.server
    -> ModuleNotFoundError: No module named 'kicad_mcp'
    KiCads gebuendeltes Python (10.0, Win) laeuft als isolierter Build und
    beachtet die PYTHONPATH-Umgebungsvariable nicht. Darum: pip-Install ok,
2026-06-13 Plugin v0.2.17: anklickbare Board-Elemente im Chat (Cross-Probe zur Editor-Auswahl)
    Feature-Wunsch: Elemente, die Claude in der Antwort nennt, als Links --
    Klick markiert sie auf der Platine. Loest das Anzeigeproblem auf grossen,
    viellagigen Boards (Antworttext sagt 'R12', aber man findet R12 nicht).
    - plugin/board_links.py (pure + headless getestet): tokenize() zerlegt
    eine Antwort in Plain-/Link-Segmente; verlinkt NUR Refs/Netze, die
    real auf dem Board existieren (je Antwort frisch via IPC geholt) ->
2026-06-13 Disk-Write-Guard: offenes .kicad_pcb nicht direkt patchen (gemeinsames Arbeiten)
    Beim gleichzeitigen Arbeiten (User in KiCad-GUI, Agent via MCP) ist der
    Platten-Text-Patcher gefaehrlich: KiCad haelt die Datei im Speicher,
    sieht externe Writes nicht, und das naechste Strg+S ueberschreibt den
    Agent-Patch (oder umgekehrt). Ein echtes Zwei-Seiten-Datei-Lock gibt es
    nicht; der Locking-Mechanismus IST der IPC-Live-Pfad (ipc_*/live_*), der
    KiCads In-Memory-Modell aendert -- eine Wahrheit, alle Fenster bleiben
2026-06-13 Task A: zentraler IPC-Session-Layer (Reuse + konfig. Timeout + Busy-Retry + File-Log)
    Behebt 'MCP nicht verbunden (failed)' auf grossen Boards und die
    Per-Call-Reconnect-Latenz. Bisher baute jeder IPC-Tool-Aufruf eine
    frische KiCad()-Verbindung mit kipys 2000-ms-Default auf (~12 Inline-
    Stellen + _connect_kicad), ohne Busy-Retry auf der breiten Flaeche.
    Neu kicad_mcp/utils/ipc_session.py:
    - get_client(): prozessweit wiederverwendeter Client; _connect_kicad()
2026-06-13 Task C: ipc_get_selection faengt den 'KiCad is busy'-Bug ab (Retry aus Task A)
    Die GUI-Selektion auf Sprachtrigger ist bereits via ipc_get_selection
    abrufbar (Refdes/Typ/Layer/Position mm-konvertiert, leere Auswahl =
    'Nichts selektiert'-Note). Einzige Luecke laut Task C war der bekannte
    kipy-Bug: Einzelselektion mancher Primitive liefert 'KiCad is busy and
    cannot respond'.
    board.get_selection() wird jetzt in ipc_session.call_with_retry (Task A,
2026-06-13 Doku: IPC-Grenzen (Live-Maus, 3D-Viewer, Schematic) als nicht-machbar festhalten
    Wie im Aufgaben-Prompt verlangt dokumentiert (nicht implementiert):
    - Live-Mausposition/Statusleisten-X/Y nicht ueber IPC exponiert; kein
    Push/Event fuer Maus/Selektion (Polling) -> Ersatz = GUI-Selektion
    (ipc_get_selection).
    - 3D-Viewer ohne API.
    - Keine Schematic-API in KiCad 10 (nur PCB-Editor).
2026-06-14 Ein-Klick-Installskripte: Plugin direkt aus dem Repo installieren
    install_plugin.bat (Windows) + install_plugin.sh (Linux/macOS) im
    Repo-Root: holen das Repo (git, sonst ZIP/tar.gz-Fallback) und kopieren
    den plugin/-Ordner (inkl. gebuendeltem mcp/) nach
    <KiCad-Config>/<ver>/scripting/plugins/claude_kicad. Erkennt eine
    lokale Checkout-Quelle, ersetzt eine vorhandene Installation idempotent,
    KiCad-Version als optionales Argument (Default 10.0). Danach nur noch
2026-06-14 CLAUDE.md: Agent-Regeln gegen Toolcall-Explosion ergaenzt (Punkt 2a, merge)
    Neuer Abschnitt 'Agent-Verhalten — gegen Toolcall-Explosion' (Render-/
    Verify-/Batch-Regeln + Loop-Vorlage Via-Platzierung) sowie Tool-Design-
    Regeln (Effekt-Echo, Batch-Varianten, Descriptions steuern Verhalten).
    Bestehende Architektur/Konventionen/Footguns/Performance bleiben
    erhalten (gemergt statt ersetzt).
    https://claude.ai/code/session_01Rxpc5X1arT1U2qtb2bFJ8H
2026-06-14 Plugin v0.2.24: Tool-Sperre reparieren + Agent-Regeln injizieren + max-turns-Bremse
    Diagnose einer entgleisten 30-Min-Session (Write/PowerShell liefen trotz
    Sperre, MCP fiel weg, Agent flailte). Drei Ursachen, autoritativ gegen
    die Claude-Code-Doku geklaert:
    1) --disallowedTools war wirkungslos: wir uebergaben EINEN komma-
    verketteten String ('Bash,Edit,Write,...'), der kein Tool matcht.
    Korrekt ist EIN Tool-Name pro argv-Wert (leerzeichengetrennt). Jetzt
2026-06-14 Revert "Plugin v0.2.24: Tool-Sperre reparieren + Agent-Regeln injizieren + max-turns-Bremse"
    This reverts commit 807eac05c71cd2eaa9a82819edb22654a2c679d6.
2026-06-14 Plugin v0.2.25: MCP-failed Ursache gefunden -- Kaltstart-Timeout-Rennen behoben
    Diagnose des Users bewies: Server startet sauber (initialize+tools/list,
    167 Tools, ~2s warm), stdout ist clean (kein Banner-Leak). 'failed:
    kicad-mcp' ist also KEIN Server-Crash, sondern ein Kaltstart-Timeout:
    Claudes MCP-Start-Timeout ist default 30s; der erste Start auf Windows
    (pandas/numpy/pywin32 + 167 Tools aus dem frisch geschriebenen _deps,
    jede .pyd von Defender gescannt) ueberschreitet das -> Server wird still
2026-06-14 Doku: menschenlesbare Versionsuebersicht (plugin/VERSIONS.md)
    Was jede Plugin-Version (0.2.0-0.2.26) gebracht hat, in einfacher Sprache
    nach Themen gruppiert (Links, Bedienung, Sicherheit, Diagnose) plus die
    Server-/Werkzeug-Meilensteine ohne eigene Versionsnummer.
    https://claude.ai/code/session_01Rxpc5X1arT1U2qtb2bFJ8H
2026-06-15 feat: Footprint-Resync-Tools (normalize_libid + refresh_pinfunctions + replace_canonical)
    Drei neue MCP-Tools = headless GUI-F8-Aequivalent ohne die SWIG-Flip-Bugs,
    nach der HOWTO-Spezifikation, an die Repo-Konventionen angepasst:
    - utils/sch_inspect.py: balanced-paren .kicad_sch-Parser
    (schematic_footprint_map: ref zu Lib:Name; schematic_pin_names:
    ref zu {nr:name} via lib_symbols-Cache, multi-unit-merge). Pure, getestet.
    - normalize_footprint_libid: bare lib_id NAME zu Lib:NAME aus dem
2026-06-15 PCM-Fix: metadata.json-Lizenz auf 'GPL-3.0' (PCM-Enum, nicht SPDX)
    Ursache von 'Archiv enthaelt keine gueltige metadata.json': KiCads PCM
    v1-Schema hat fuer 'license' eine FESTE Enum-Liste, KEIN SPDX. Unser
    'GPL-3.0-or-later' ist nicht erlaubt -> KiCad verwirft die metadata.json.
    (Nicht Windows-spezifisch; gegen das echte Schema validiert.)
    Erlaubter Wert ist 'GPL-3.0'. Verifiziert: metadata.json passiert jetzt
    das vollstaendige pcm.v1.schema.json (jsonschema). Neuer
2026-06-15 Plugin v0.2.28: Batch als UTF-8 schreiben (Umlaut im Windows-Benutzernamen)
    Bug: Deps-Install scheiterte bei Benutzer 'Schueler' (mit Umlaut) mit
    WinError 123 - der _deps-Pfad C:\Users\<umlaut> wurde zu C:\Users\Sch?ler
    (? = ungueltiges Windows-Pfadzeichen). Ursache war NICHT cmd.exe, sondern
    unser _write_temp_bat in terminal.py: encoding='ascii', errors='replace'
    ersetzte jedes Nicht-ASCII-Zeichen durch ?, obwohl die Batch oben schon
    chcp 65001 (UTF-8) setzt.
2026-06-15 Plugin v0.2.30: Deps-Check injiziert sys.path in-process (PYTHONPATH wird ignoriert)
    Symptom: Nach erfolgreicher Installation (_deps voll befüllt, Server-Probe OK
    mit 167 Tools) meldete die Checkliste die Abhängigkeiten weiter als 'fehlt' →
    Endlos-Neuinstallation.
    Ursache: deps.check_deps legte _deps nur über PYTHONPATH auf den Suchpfad.
    KiCads gebündeltes Python ignoriert PYTHONPATH (isolierter ._pth-Build) — der
    find_spec-Probe lief ohne _deps auf sys.path und meldete alles fehlend. Der
2026-06-16 Plugin v0.2.31: Deps-Install ganz ohne cmd/Batch (direkter Subprozess)
    Baut auf dem Env-Variablen-Fix (v0.2.29/0.2.30) auf und ersetzt den
    Install-Pfad durch einen direkten Subprozess: pip install --target und die
    Import-Pruefung gehen als argv-Liste an subprocess.Popen (kein Shell, kein
    .bat). Windows reicht den Unicode-Pfad ueber CreateProcessW unverfaelscht
    durch, sodass ein Umlaut (C:\Users\Schueler) strukturell nicht mehr zu "?"
    gefaltet werden kann (WinError 123).
2026-06-16 Einweisungs-MD fuer Live-Fix der klickbaren Board-Links
    plugin/FIX_LINKS_BRIEFING.md: Handoff fuer ein lokales Claude Code mit
    echtem KiCad/kipy-Zugriff. Beschreibt Symptome, Architektur (board_links.py
    pure + kipy, chat_dialog Flow), die zu pruefenden kipy-0.7.1-API-Annahmen,
    ein Live-Diagnose-Snippet, erwartete Fixpfade (inkl. Pins), Mock-Nachzug +
    Akzeptanzkriterien und die Projektkonventionen. Das Link-Problem ist rein
    live (Unit-Tests gegen Mocks gruen), daher nur dort verifizierbar.
2026-06-16 Chat-Link-Diagnose: stillen Fall 'Board-Daten da, aber 0 Treffer im Reply' sichtbar machen
    _append_claude gibt die Zahl gerenderter Link-Spans zurück; _on_reply meldet
    'ⓘ Links: r Refs / n Netze / ly Layer gelesen, aber 0 im Antworttext erkannt',
    wenn Board-Daten vorlagen (Counts > 0), aber nichts linkifiziert wurde — bisher
    ohne Diagnose-Zeile (= genau das gemeldete Symptom).
2026-06-16 v0.3.2: Chat-Link Disk-Fallback — Links rendern auch ohne Live-IPC
    Ursache von 'nichts orange': der kipy-Client des Chat-Panels (board_links.
    connect()) geht bei mehreren KiCad-Instanzen leer aus, waehrend der MCP-Server
    das Board aus der Datei liest. Neuer board_targets_from_file() parst Refs/Netze/
    Layer aus der .kicad_pcb; _worker faellt darauf zurueck, wenn Live-IPC fehlt
    oder 0 liefert. tokenize ist headless als korrekt verifiziert. ⓘ-Zeile weist
    die Disk-Quelle aus. 4 neue Tests.
